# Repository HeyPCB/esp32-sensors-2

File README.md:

# HeyPCB ESP32-S3 Sensors 2: Motion, Magnetic, Optical & Power

50 ESP32-S3 boards, one sensor each: IMUs, accelerometers, magnetometers, Hall and angle sensors, distance, touch, optical and current monitors. KiCad 10, JLCPCB-ready, CERN-OHL-S-2.0.

Every board is the same ESP32-S3 template with one sensor: ESP32-S3-WROOM-1-N16R8 (16 MB flash, 8 MB PSRAM, Wi-Fi + Bluetooth LE), USB-C with native USB and an ESD clamp, an AP2112K 3.3 V LDO, BOOT and RESET buttons, power and user LEDs; 30 x 48 mm, 4 layers.

| Wiring | ESP32-S3 pin |
|---|---|
| I2C SDA / SCL | IO8 / IO9 |
| Sensor interrupt | IO7 |
| Analog in | IO1 (ADC1 channel 0) |
| SPI SCK / MOSI / MISO / CS | IO12 / IO11 / IO13 / IO10 |
| Digital / 1-Wire / PDM | IO4, IO5, IO6 |
| User LED | IO48 |

## Boards (50)

| Board | Sensor | DRC errors / unconnected / parity |
|---|---|---|
| [S3 A1324](boards/a1324/) | Allegro A1324 low-noise linear Hall sensor | 0 / 0 / 0 |
| [S3 A3214](boards/a3214/) | Allegro A3214 micropower omnipolar Hall switch | 0 / 0 / 0 |
| [S3 ADS1115](boards/ads1115/) | TI ADS1115 16-bit 4-channel ADC | 0 / 0 / 0 |
| [S3 ADXL343](boards/adxl343/) | ADI ADXL343 3-axis accelerometer | 0 / 0 / 0 |
| [S3 ADXL345](boards/adxl345/) | ADI ADXL345 3-axis accelerometer | 0 / 0 / 0 |
| [S3 AH1806](boards/ah1806/) | Diodes AH1806 omnipolar Hall switch | 0 / 0 / 0 |
| [S3 AS5047D](boards/as5047d/) | ams AS5047D 14-bit magnetic encoder (SPI and ABI) | 0 / 0 / 0 |
| [S3 AS5600](boards/as5600/) | ams AS5600 12-bit magnetic angle sensor | 0 / 0 / 0 |
| [S3 QT1010](boards/at42qt1010/) | Microchip AT42QT1010 single-key capacitive touch sensor | 0 / 0 / 0 |
| [S3 BNO055](boards/bno055/) | Bosch BNO055 9-axis absolute orientation sensor | 0 / 0 / 0 |
| [S3 BPW34](boards/bpw34/) | Vishay BPW34 through-hole silicon photodiode light sensor | 0 / 0 / 0 |
| [S3 BPW34S](boards/bpw34s/) | Osram BPW34S silicon photodiode light sensor | 0 / 0 / 0 |
| [S3 CNY70](boards/cny70/) | Vishay CNY70 reflective optical sensor | 0 / 0 / 0 |
| [S3 DRV5032](boards/drv5032/) | TI DRV5032 ultra-low-power Hall switch | 0 / 0 / 0 |
| [S3 DRV5055](boards/drv5055/) | TI DRV5055 ratiometric linear Hall sensor | 0 / 0 / 0 |
| [S3 DRV5055A2](boards/drv5055a2/) | TI DRV5055A2 ratiometric linear Hall sensor (+-31 mT) | 0 / 0 / 0 |
| [S3 FLAME](boards/flame/) | Everlight PD333-3C infrared photodiode flame sensor | 0 / 0 / 0 |
| [S3 ICM-20602](boards/icm20602/) | TDK ICM-20602 6-axis IMU | 0 / 0 / 0 |
| [S3 ICM-20948](boards/icm20948/) | TDK ICM-20948 9-axis IMU | 0 / 0 / 0 |
| [S3 ICM-42688](boards/icm42688/) | TDK ICM-42688-P high-precision 6-axis IMU | 0 / 0 / 0 |
| [S3 IIM-42652](boards/iim42652/) | TDK IIM-42652 industrial 6-axis IMU | 0 / 0 / 0 |
| [S3 IIS3DWB](boards/iis3dwb/) | ST IIS3DWB wideband vibration sensor (6 kHz) | 0 / 0 / 0 |
| [S3 INA219](boards/ina219/) | TI INA219 load current and voltage monitor | 0 / 0 / 0 |
| [S3 INA226](boards/ina226/) | TI INA226 load current, voltage and power monitor | 0 / 0 / 0 |
| [S3 INA233](boards/ina233/) | TI INA233 PMBus current, voltage, power and energy monitor | 0 / 0 / 0 |
| [S3 INA237](boards/ina237/) | TI INA237 85 V current, voltage and power monitor | 0 / 0 / 0 |
| [S3 INA238](boards/ina238/) | TI INA238 85 V high-precision power monitor | 0 / 0 / 0 |
| [S3 KX022](boards/kx022/) | Kionix KX022-1020 3-axis accelerometer | 0 / 0 / 0 |
| [S3 LIS2DH12](boards/lis2dh12/) | ST LIS2DH12 ultra-low-power 3-axis accelerometer | 0 / 0 / 0 |
| [S3 LIS2HH12](boards/lis2hh12/) | ST LIS2HH12 3-axis accelerometer | 0 / 0 / 0 |
| [S3 LIS2MDL](boards/lis2mdl/) | ST LIS2MDL 3-axis magnetometer | 0 / 0 / 0 |
| [S3 LIS3DH](boards/lis3dh/) | ST LIS3DH 3-axis accelerometer with ADC inputs | 0 / 0 / 0 |
| [S3 LIS3MDL](boards/lis3mdl/) | ST LIS3MDL 3-axis magnetometer | 0 / 0 / 0 |
| [S3 LSM6DS3](boards/lsm6ds3/) | ST LSM6DS3TR-C 6-axis IMU | 0 / 0 / 0 |
| [S3 LSM6DSL](boards/lsm6dsl/) | ST LSM6DSL 6-axis IMU | 0 / 0 / 0 |
| [S3 LSM6DSOX](boards/lsm6dsox/) | ST LSM6DSOX 6-axis IMU with machine-learning core | 0 / 0 / 0 |
| [S3 MPR121](boards/mpr121/) | NXP MPR121 12-channel capacitive touch controller | 0 / 0 / 0 |
| [S3 MPU-6000](boards/mpu6000/) | InvenSense MPU-6000 6-axis IMU (SPI and I2C) | 0 / 0 / 0 |
| [S3 MPU6050](boards/mpu6050/) | InvenSense MPU-6050 6-axis IMU | 0 / 0 / 0 |
| [S3 18B20Z](boards/my18b20z/) | MY18B20Z 1-Wire temperature sensor (SOIC-8) | 0 / 0 / 0 |
| [S3 SFH320](boards/sfh320/) | ams OSRAM SFH 320 SMD phototransistor light sensor | 0 / 0 / 0 |
| [S3 SM351LT](boards/sm351lt/) | Honeywell SM351LT nanopower magnetoresistive switch | 0 / 0 / 0 |
| [S3 SS49E](boards/ss49e/) | SS49E linear Hall effect sensor | 0 / 0 / 0 |
| [S3 TEPT4400](boards/tept4400/) | Vishay TEPT4400 ambient light phototransistor | 0 / 0 / 0 |
| [S3 TLV493D](boards/tlv493d/) | Infineon TLV493D 3D magnetic sensor | 0 / 0 / 0 |
| [S3 TMAG5111](boards/tmag5111/) | TI TMAG5111 2D Hall latch (rotary encoder sensor) | 0 / 0 / 0 |
| [S3 TSOP38238](boards/tsop38238/) | Vishay TSOP38238 38 kHz IR remote-control receiver | 0 / 0 / 0 |
| [S3 VL53L0X](boards/vl53l0x/) | ST VL53L0X 2 m time-of-flight distance sensor | 0 / 0 / 0 |
| [S3 ToF](boards/vl53l1x/) | VL53L1X 4 m time-of-flight distance sensor | 0 / 0 / 0 |
| [S3 VL53L4CD](boards/vl53l4cd/) | ST VL53L4CD 1.3 m time-of-flight distance sensor | 0 / 0 / 0 |

**Not fabricated, assembled or powered.** Every number in a board's README is measured by KiCad 10 on the files in its folder (`report.json`); parts carry LCSC numbers and were in JLCPCB's stock on the date each README gives.

Each board folder holds `kicad/` (project), `fab/` (Gerbers zip, BOM, CPL, STEP, schematic PDF), `media/` (renders) and `board.json` (the brief it was generated from).

Designed with the HeyPCB method on KiCad 10 by heypcb-kicad's headless pipeline with Freerouting 2.4.1.

## Licence

CERN-OHL-S-2.0, © 2026 heypcb.ai. See [LICENSE](LICENSE).

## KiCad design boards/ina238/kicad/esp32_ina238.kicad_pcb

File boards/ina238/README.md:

# S3 INA238

An ESP32-S3 board with TI INA238 85 V high-precision power monitor: USB-C, Wi-Fi and Bluetooth LE, ready to flash.

| Layers | Size | Parts | Nets | Connections routed | Vias | ERC errors | DRC errors / unconnected / parity |
|---|---|---|---|---|---|---|---|
| 4 | 30 x 60 mm | 26 | 17 | 76 -> 0 open | 41 | 0 | 0 / 0 / 0 |

**Not fabricated, assembled or powered.** Every number on this page is measured by KiCad 10 on the files in this folder; the full measurements are in [`report.json`](report.json).

| | |
|---|---|
| KiCad project | [`kicad/`](kicad/) |
| Gerbers, BOM, CPL, STEP, schematic PDF | [`fab/`](fab/) |
| Renders | [top](media/top.png), [bottom](media/bottom.png) |

A small ESP32-S3 development board built around one sensor: TI INA238 85 V high-precision power monitor. Plug in USB-C, flash it from Arduino, ESP-IDF or MicroPython over the ESP32-S3's native USB, and read the sensor. One of the HeyPCB ESP32 sensor series: the same ESP32-S3 template with a different sensor on each board. Designed with the HeyPCB method on KiCad 10, by heypcb-kicad's headless pipeline with Freerouting 2.4.1, from the brief in `board.json`.

## Specs

- **MCU:** ESP32-S3-WROOM-1-N16R8 (16 MB flash, 8 MB PSRAM, Wi-Fi + BLE 5), antenna over the top edge with no copper under it.
- **USB:** USB-C, native USB on the ESP32-S3 (no bridge chip), USBLC6-2 ESD clamp; BOOT (IO0) and RESET buttons.
- **Power:** USB 5 V to an AP2112K 3.3 V / 600 mA LDO; green power LED, blue user LED on IO48.
- **Sensor:** TI INA238 85 V high-precision power monitor. Wired to the ESP32-S3: I2C_SCL on IO9, I2C_SDA on IO8, SNS_INT on IO7.
- **Board:** 30 x 60 mm, 4 layers (In1 GND plane), 1.6 mm.
- **Sensor notes:** INA238 (TI datasheet): 16-bit, A0 = A1 = GND gives address 0x40; shunt full scale +-163.84 mV = 16 A on 10 mOhm; ALERT open drain, 10k pull-up, to IO7; 100 nF on VS.
- **Sensor notes:** The load current runs supply + -> terminal pin 1 -> 10 mOhm 1 W shunt -> terminal pin 2 -> load +, with ground on pin 3. Tracks on the load path are 1.0 mm: the board is made for up to 3 A.

## Parts

Every line carries an LCSC part number. Stock is JLCPCB's assembly stock on 2026-10-18.

| Designators | Value | LCSC | MPN | JLCPCB tier | Stock |
|---|---|---|---|---|---|
| C1 | 10uF | C15850 | CL21A106KAYNNNE | Basic | 6,481,857 |
| C2,C3,C6 | 1uF | C15849 | CL10A105KB8NNNC | Basic | 9,242,432 |
| C4 | 100nF | C14663 | CC0603KRX7R9BB104 | Basic | 32,334,212 |
| C5 | 22uF | C45783 | CL21A226MAQNNNE | Basic | 3,755,608 |
| C7 | 100nF | C1525 | CL05B104KO5NNNC | Basic | 29,476,420 |
| D1 | Blue (IO48) | C84266 | NCD0603B1 | Extended | 226,365 |
| D2 | Green (PWR) | C12624 | KT-0603G | Extended | 499,725 |
| J1 | USB-C | C165948 | TYPE-C-31-M-12 | Extended | 357,307 |
| J2 | IN OUT GND | C5188435 | MX126-5.0-03P-GN01-Cu-S-A | Extended | 12,798 |
| R1,R2 | 5.1k | C25905 | 0402WGF5101TCE | Basic | 5,086,543 |
| R3,R6 | 10k | C25804 | 0603WAF1002T5E | Basic | 39,931,112 |
| R4 | 1k | C21190 | 0603WAF1001T5E | Basic | 23,204,357 |
| R5 | 2.2k | C4190 | 0603WAF2201T5E | Basic | 6,534,948 |
| R7 | 10m | C105362 | FMF06FTHR010-LH | Extended | 145,279 |
| R8,R9 | 4.7k | C23162 | 0603WAF4701T5E | Basic | 18,613,172 |
| SW1 | BOOT | C318884 | TS-1187A-B-A-B | Basic | 290,976 |
| SW2 | RESET | C318884 | TS-1187A-B-A-B | Basic | 290,976 |
| U1 | USBLC6-2SC6 | C7519 | USBLC6-2SC6 | Extended | 33,518 |
| U2 | AP2112K-3.3 | C51118 | AP2112K-3.3TRG1 | Extended | 6,345 |
| U3 | ESP32-S3-WROOM-1-N16R8 | C2913202 | ESP32-S3-WROOM-1-N16R8 | Extended | 32,329 |
| U4 | INA238AIDGSR | C2868250 | INA238AIDGSR | Extended | 1,134 |

## Ordering

- PCB: upload `fab/esp32_ina238_gerbers.zip`, 4 layers, 30 x 60 mm, 1.6 mm.
- Assembly: `fab/esp32_ina238_bom.csv` and `fab/esp32_ina238_cpl_jlc.csv`, top side.
- The CPL is fitted to each part's own JLCPCB footprint, pad by pad, and re-checked by laying each footprint where its row says: 24 of 26 rows fitted, worst pin-to-pad offset 0.20 mm.
- Not fitted (no JLCPCB footprint to fit to), rotation from KiCad's: SW1, SW2. Check these in JLCPCB's placement preview.

## Notes

- The two TS-1187A buttons are placed with KiCad's rotation: KiCad's footprint and JLCPCB's land share a frame (pads at x +-3.0, y +-1.85 mm), but the automatic fit cannot confirm it because KiCad numbers the pads 1, 1, 2, 2.
- The USB-C receptacle renders as a plain box: KiCad's footprint names a 3D model KiCad does not ship.
- Not built or measured.

## How it was made

Designed with the HeyPCB method on KiCad 10, by heypcb-kicad's headless pipeline with Freerouting 2.4.1, from the brief in [`board.json`](board.json).

## Licence

CERN-OHL-S-2.0, © 2026 heypcb.ai. See the collection's LICENSE.

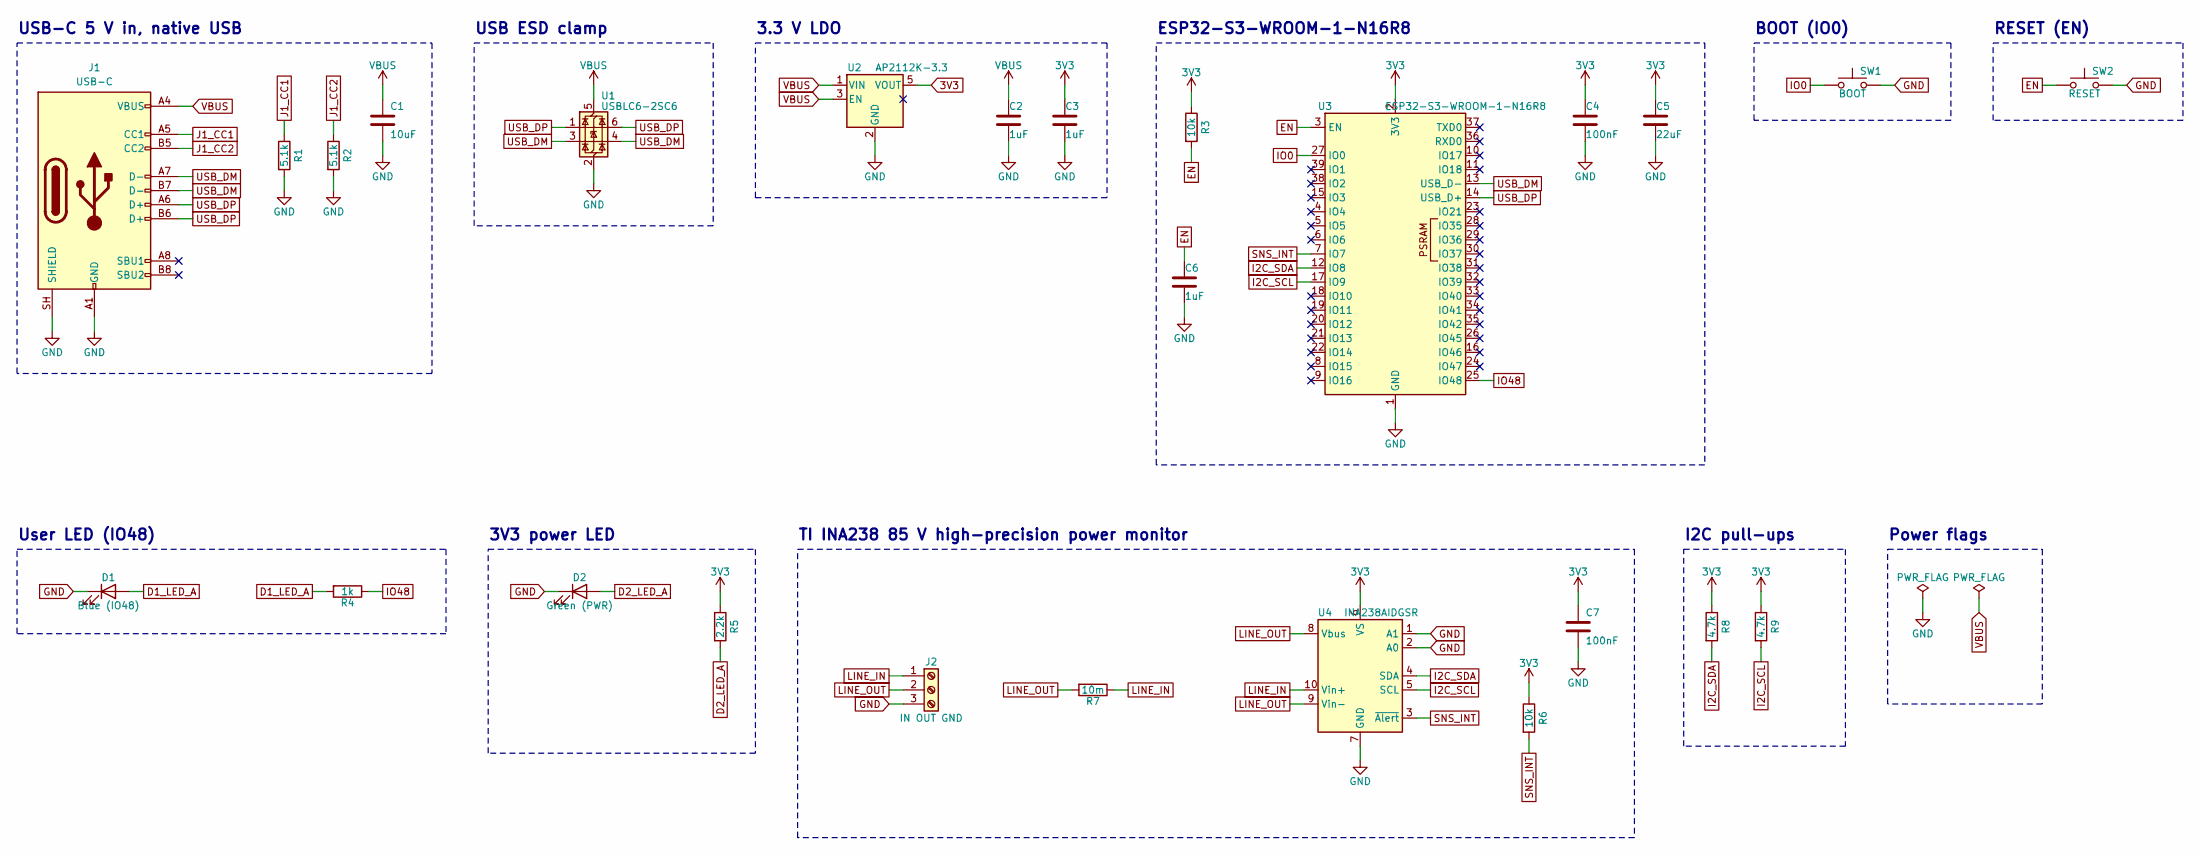
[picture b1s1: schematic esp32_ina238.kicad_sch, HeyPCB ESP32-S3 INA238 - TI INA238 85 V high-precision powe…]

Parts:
C1: 10uF; C_0805_2012Metric; MPN CL21A106KAYNNNE; LCSC C15850
C2, C3, C6: 1uF; C_0603_1608Metric; MPN CL10A105KB8NNNC; LCSC C15849
C4: 100nF; C_0603_1608Metric; MPN CC0603KRX7R9BB104; LCSC C14663
C5: 22uF; C_0805_2012Metric; MPN CL21A226MAQNNNE; LCSC C45783
C7: 100nF; C_0402_1005Metric; MPN CL05B104KO5NNNC; LCSC C1525
D1: Blue (IO48); LED_0603_1608Metric; MPN NCD0603B1; LCSC C84266
D2: Green (PWR); LED_0603_1608Metric; MPN KT-0603G; LCSC C12624
J1: USB-C; USB_C_Receptacle_HRO_TYPE-C-31-M-12; MPN TYPE-C-31-M-12; LCSC C165948
J2: IN OUT GND; TerminalBlock_MaiXu_MX126-5.0-03P_1x03_P5.00mm; MPN MX126-5.0-03P-GN01-Cu-S-A; LCSC C5188435
R1, R2: 5.1k; R_0402_1005Metric; MPN 0402WGF5101TCE; LCSC C25905
R3, R6: 10k; R_0603_1608Metric; MPN 0603WAF1002T5E; LCSC C25804
R4: 1k; R_0603_1608Metric; MPN 0603WAF1001T5E; LCSC C21190
R5: 2.2k; R_0603_1608Metric; MPN 0603WAF2201T5E; LCSC C4190
R7: 10m; R_1206_3216Metric; MPN FMF06FTHR010-LH; LCSC C105362
R8, R9: 4.7k; R_0603_1608Metric; MPN 0603WAF4701T5E; LCSC C23162
SW1: BOOT; SW_Push_1P1T_XKB_TS-1187A; MPN TS-1187A-B-A-B; LCSC C318884
SW2: RESET; SW_Push_1P1T_XKB_TS-1187A; MPN TS-1187A-B-A-B; LCSC C318884
U1: USBLC6-2SC6; SOT-23-6; MPN USBLC6-2SC6; LCSC C7519
U2: AP2112K-3.3; SOT-23-5; MPN AP2112K-3.3TRG1; LCSC C51118
U3: ESP32-S3-WROOM-1-N16R8; ESP32-S3-WROOM-1; MPN ESP32-S3-WROOM-1-N16R8; LCSC C2913202
U4: INA238AIDGSR; TSSOP-10_3x3mm_P0.5mm; MPN INA238AIDGSR; LCSC C2868250

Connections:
3V3: C3.1, C4.1, C5.1, C7.1, R3.1, R5.1, R6.1, R8.1, R9.1, U2.5 (VOUT), U3.2 (3V3), U4.6 (VS)
D1_LED_A: D1.2 (A), R4.2
D2_LED_A: D2.2 (A), R5.2
EN: C6.1, R3.2, SW2.1, U3.3 (EN)
GND: C1.2, C2.2, C3.2, C4.2, C5.2, C6.2, C7.2, D1.1 (K), D2.1 (K), J1.A1 (GND), J1.A12 (GND), J1.B1 (GND), J1.B12 (GND), J1.SH (SHIELD), J2.3, R1.2, R2.2, SW1.2, SW2.2, U1.2 (GND), U2.2 (GND), U3.1 (GND), U3.40 (GND), U3.41 (GND), U4.1 (A1), U4.2 (A0), U4.7 (GND)
I2C_SCL: R9.2, U3.17 (IO9), U4.5 (SCL)
I2C_SDA: R8.2, U3.12 (IO8), U4.4 (SDA)
IO0: SW1.1, U3.27 (IO0)
IO48: R4.1, U3.25 (IO48)
J1_CC1: J1.A5 (CC1), R1.1
J1_CC2: J1.B5 (CC2), R2.1
LINE_IN: J2.1, R7.1, U4.10 (Vin+)
LINE_OUT: J2.2, R7.2, U4.8 (Vbus), U4.9 (Vin-)
SNS_INT: R6.2, U3.7 (IO7), U4.3 (~Alert)
USB_DM: J1.A7 (D-), J1.B7 (D-), U1.3 (I/O2), U1.4 (I/O2), U3.13 (USB_D-)
USB_DP: J1.A6 (D+), J1.B6 (D+), U1.1 (I/O1), U1.6 (I/O1), U3.14 (USB_D+)
VBUS: C1.1, C2.1, J1.A4 (VBUS), J1.A9 (VBUS), J1.B4 (VBUS), J1.B9 (VBUS), U1.5 (VBUS), U2.1 (VIN), U2.3 (EN)

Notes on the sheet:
USB-C 5 V in, native USB
USB ESD clamp
3.3 V LDO
ESP32-S3-WROOM-1-N16R8
BOOT (IO0)
RESET (EN)
User LED (IO48)
3V3 power LED
TI INA238 85 V high-precision power monitor
I2C pull-ups
Power flags

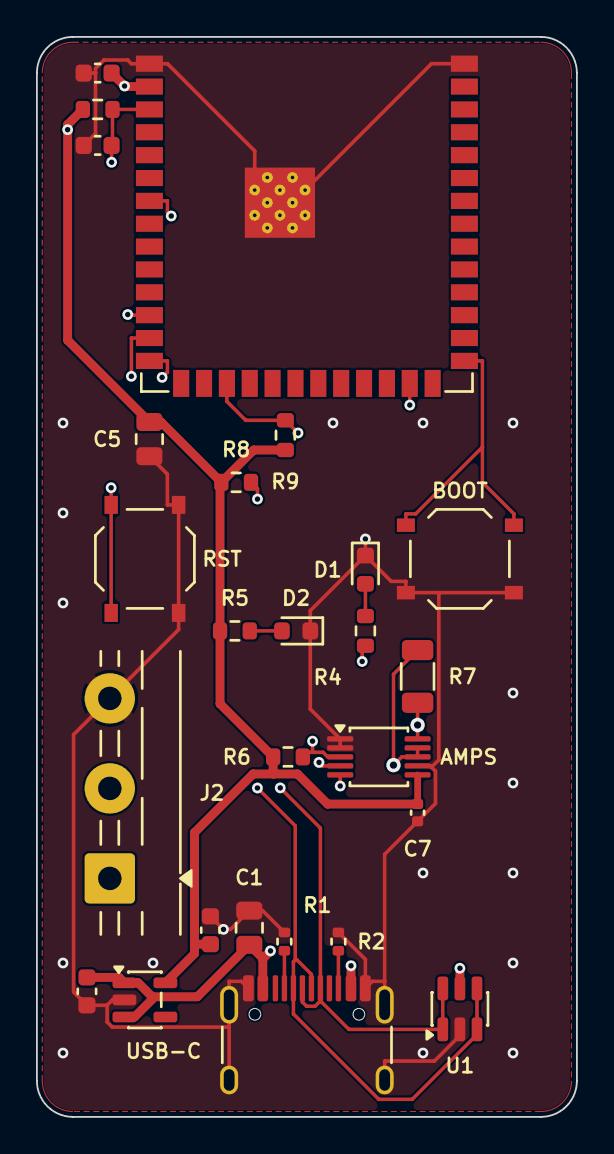
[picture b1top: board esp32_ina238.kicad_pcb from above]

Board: 4 copper layers, 30.0 x 60.0 mm, 26 parts (0 on the bottom side), 17 nets.

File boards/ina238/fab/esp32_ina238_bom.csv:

"Reference","Value","Footprint","MPN","LCSC","Qty"
"C1","10uF","Capacitor_SMD:C_0805_2012Metric","CL21A106KAYNNNE","C15850","1"
"C2,C3,C6","1uF","Capacitor_SMD:C_0603_1608Metric","CL10A105KB8NNNC","C15849","3"
"C4","100nF","Capacitor_SMD:C_0603_1608Metric","CC0603KRX7R9BB104","C14663","1"
"C5","22uF","Capacitor_SMD:C_0805_2012Metric","CL21A226MAQNNNE","C45783","1"
"C7","100nF","Capacitor_SMD:C_0402_1005Metric","CL05B104KO5NNNC","C1525","1"
"D1","Blue (IO48)","LED_SMD:LED_0603_1608Metric","NCD0603B1","C84266","1"
"D2","Green (PWR)","LED_SMD:LED_0603_1608Metric","KT-0603G","C12624","1"
"J1","USB-C","Connector_USB:USB_C_Receptacle_HRO_TYPE-C-31-M-12","TYPE-C-31-M-12","C165948","1"
"J2","IN OUT GND","TerminalBlock:TerminalBlock_MaiXu_MX126-5.0-03P_1x03_P5.00mm","MX126-5.0-03P-GN01-Cu-S-A","C5188435","1"
"R1,R2","5.1k","Resistor_SMD:R_0402_1005Metric","0402WGF5101TCE","C25905","2"
"R3,R6","10k","Resistor_SMD:R_0603_1608Metric","0603WAF1002T5E","C25804","2"
"R4","1k","Resistor_SMD:R_0603_1608Metric","0603WAF1001T5E","C21190","1"
"R5","2.2k","Resistor_SMD:R_0603_1608Metric","0603WAF2201T5E","C4190","1"
"R7","10m","Resistor_SMD:R_1206_3216Metric","FMF06FTHR010-LH","C105362","1"
"R8,R9","4.7k","Resistor_SMD:R_0603_1608Metric","0603WAF4701T5E","C23162","2"
"SW1","BOOT","Button_Switch_SMD:SW_Push_1P1T_XKB_TS-1187A","TS-1187A-B-A-B","C318884","1"
"SW2","RESET","Button_Switch_SMD:SW_Push_1P1T_XKB_TS-1187A","TS-1187A-B-A-B","C318884","1"
"U1","USBLC6-2SC6","Package_TO_SOT_SMD:SOT-23-6","USBLC6-2SC6","C7519","1"
"U2","AP2112K-3.3","Package_TO_SOT_SMD:SOT-23-5","AP2112K-3.3TRG1","C51118","1"
"U3","ESP32-S3-WROOM-1-N16R8","RF_Module:ESP32-S3-WROOM-1","ESP32-S3-WROOM-1-N16R8","C2913202","1"
"U4","INA238AIDGSR","Package_SO:TSSOP-10_3x3mm_P0.5mm","INA238AIDGSR","C2868250","1"
